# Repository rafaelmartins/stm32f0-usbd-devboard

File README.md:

# stm32f0-usbd-devboard

A simple devboard for USB projects based on STM32F042

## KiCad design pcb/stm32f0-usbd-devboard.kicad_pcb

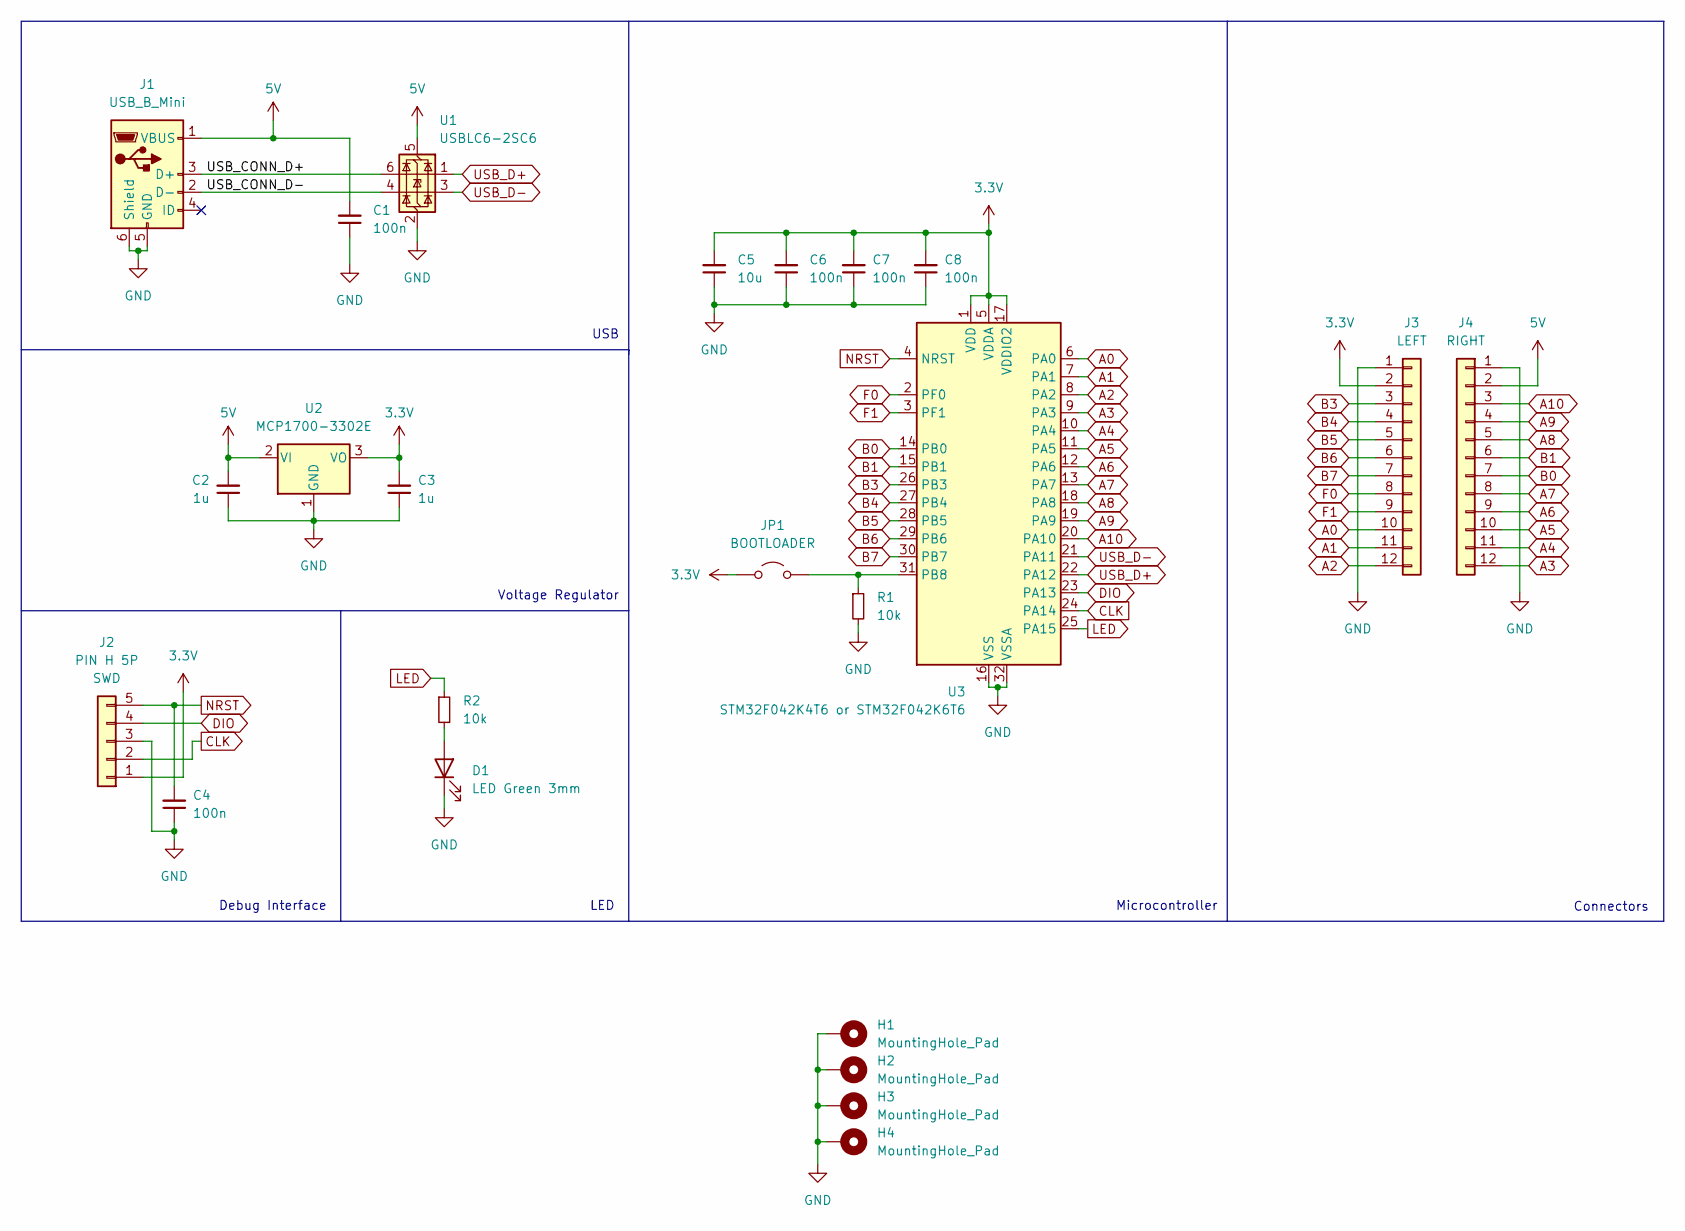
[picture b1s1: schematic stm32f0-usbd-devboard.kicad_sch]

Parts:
C1, C4, C6, C7, C8: 100n; C_TDK_FA28; MPN FA28X7R1H104KNU06
C2, C3: 1u; C_TDK_FA28; MPN FA28X7R1E105KRU06
C5: 10u; C_TDK_FA26; MPN FA26X7R1E106KRU06
D1: LED Green 3mm; LED_D3.0mm_Horizontal_O1.27mm_Z2.0mm; MPN OVLBG4C7
H1, H2, H3, H4: MountingHole_Pad; MountingHole_2.2mm_M2_Pad_Via
J1: USB_B_Mini; USB_Mini-B_PTH; MPN GMSB0522132EU
J2: PIN H 5P; PinHeader_SWD_1x05_P2.54mm_Vertical
J3: LEFT; PinHeader_DevBoard_Left_Connector_1x12_P2.54mm_Vertical
J4: RIGHT; PinHeader_DevBoard_Right_Connector_1x12_P2.54mm_Vertical
JP1: BOOTLOADER; PinHeader_1x02_P2.54mm_Vertical
R1, R2: 10k; R_YAGEO_MFR-25FTE52_Horizontal; MPN MFR-25FTE52-10K
U1: USBLC6-2SC6; SOT-23-6; MPN USBLC6-2SC6
U2: MCP1700-3302E; TO-92_Inline_Wide; MPN MCP1700-3302E/TO
U3: STM32F042K4T6 or STM32F042K6T6; LQFP-32_7x7mm_P0.8mm; MPN STM32F042K6T6

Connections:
3.3V: C3.2, C5.2, C6.2, C7.2, C8.2, J2.1, J3.2, JP1.2 (B), U2.3 (VO), U3.1 (VDD), U3.5 (VDDA), U3.17 (VDDIO2)
5V: C1.2, C2.2, J1.1 (VBUS), J4.2, U1.5 (VBUS), U2.2 (VI)
/USB_CONN_D+: J1.3 (D+), U1.6 (I/O1)
/USB_CONN_D-: J1.2 (D-), U1.4 (I/O2)
A0: J3.10, U3.6 (PA0)
A1: J3.11, U3.7 (PA1)
A2: J3.12, U3.8 (PA2)
A3: J4.12, U3.9 (PA3)
A4: J4.11, U3.10 (PA4)
A5: J4.10, U3.11 (PA5)
A6: J4.9, U3.12 (PA6)
A7: J4.8, U3.13 (PA7)
A8: J4.5, U3.18 (PA8)
A9: J4.4, U3.19 (PA9)
A10: J4.3, U3.20 (PA10)
B0: J4.7, U3.14 (PB0)
B1: J4.6, U3.15 (PB1)
B3: J3.3, U3.26 (PB3)
B4: J3.4, U3.27 (PB4)
B5: J3.5, U3.28 (PB5)
B6: J3.6, U3.29 (PB6)
B7: J3.7, U3.30 (PB7)
CLK: J2.2, U3.24 (PA14)
DIO: J2.4, U3.23 (PA13)
F0: J3.8, U3.2 (PF0)
F1: J3.9, U3.3 (PF1)
GND: C1.1, C2.1, C3.1, C4.1, C5.1, C6.1, C7.1, C8.1, D1.1 (K), H1.1, H2.1, H3.1, H4.1, J1.5 (GND), J1.6 (Shield), J2.3, J3.1, J4.1, R1.2, U1.2 (GND), U2.1 (GND), U3.16 (VSS), U3.32 (VSSA)
LED: R2.1, U3.25 (PA15)
NRST: C4.2, J2.5, U3.4 (NRST)
unnamed: D1.2 (A), R2.2
unnamed: JP1.1 (A), R1.1, U3.31 (PB8)
USB_D+: U1.1 (I/O1), U3.22 (PA12)
USB_D-: U1.3 (I/O2), U3.21 (PA11)

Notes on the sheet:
Debug Interface
LED
Microcontroller
Connectors
Voltage Regulator
USB

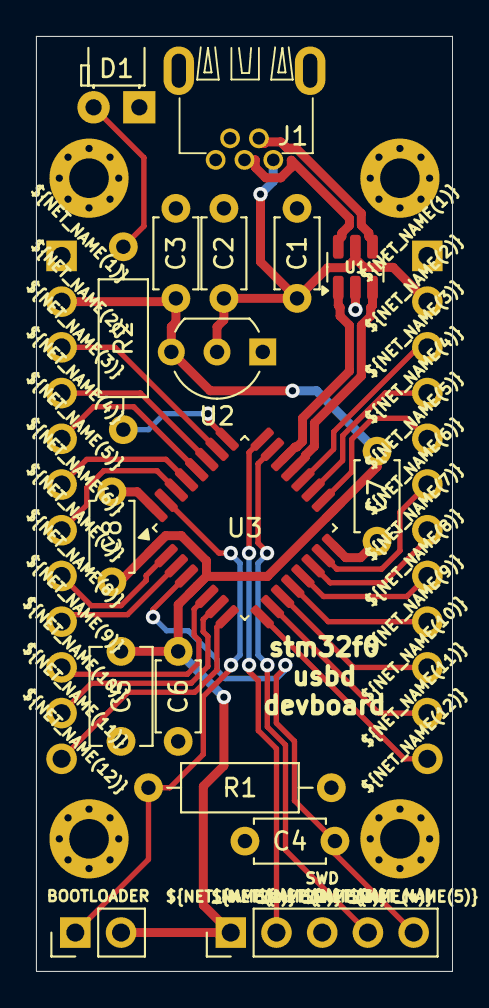
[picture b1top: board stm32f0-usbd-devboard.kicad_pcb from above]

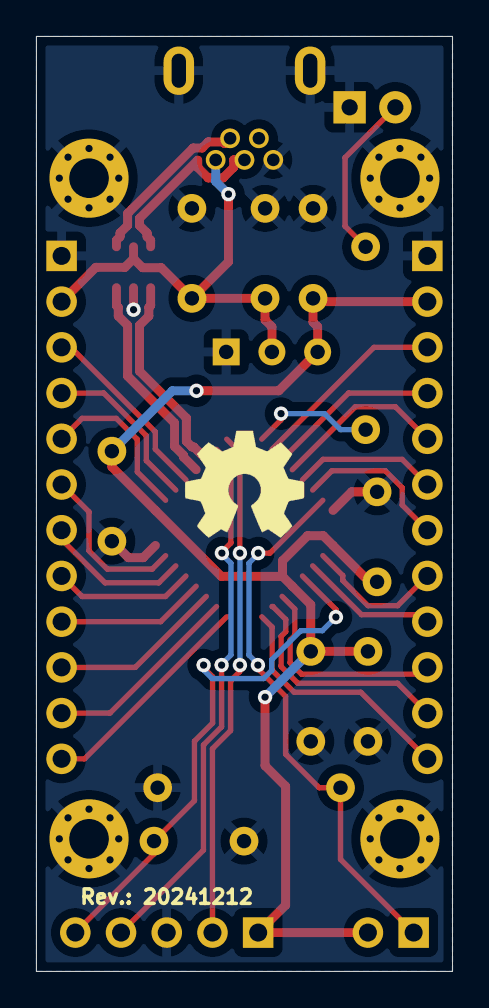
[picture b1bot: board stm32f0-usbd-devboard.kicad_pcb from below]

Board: 2 copper layers, 23.1 x 51.9 mm, 23 parts (2 on the bottom side), 33 nets.

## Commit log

2024-12-10 initial commit. revision 20241210
    pcb is optimized for handwired devices, not for protoboard usage, despite fitting on it.
    a new protoboard-focused revision may be created at some point.
2024-12-12 pcb: remove unused footprint
2024-12-12 pcb: revision 20241212
    new protoboard-friendly pcb revision.
2025-02-26 pcb: upgrade to kicad 9
2025-02-26 upgrade footprints to kicad 9

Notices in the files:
pcb/stm32f0-usbd-devboard.kicad_pcb:
Released under CERN Open Hardware Licence Version 2 - Strongly Reciprocal
